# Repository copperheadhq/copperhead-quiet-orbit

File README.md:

# Quiet Orbit QO-R1

A USB-C powered desk ornament: four amber LEDs at the corners of a 40 mm square, each on its
own hardware-PWM channel of an ATtiny84A, fading independently on four phases. 57 × 57 mm,
two layers, no data, no PD, no radio, no battery, no controls.

> ## ⚠ This board has never been built
>
> No PCB has been fabricated from these files. Nothing has been powered on. The firmware has
> never been compiled, because no AVR toolchain was available where it was written, and it has
> never run on hardware. Every manufacturer part number in the BOM is marked **UNVERIFIED** by its own
> author, and at least one fitted part is known to be the wrong choice.
>
> The files pass ERC and DRC. That means the copper is consistent with the schematic and with
> a set of design rules. It is not evidence that the circuit works.
>
> **Do not order this board expecting a working lamp.** Order it to look at, to fork, or to
> fix.

Quick facts: [docs/QO-R1-summary.pdf](docs/QO-R1-summary.pdf). Everything: [docs/QO-R1-reference.pdf](docs/QO-R1-reference.pdf).

## Background

On 21 September 2026, Paras Chopra [posted](https://x.com/paraschopra/status/2101906787050115492)
that he had asked an AI model he calls Astra to design a piece of hardware for itself. It chose
four softly blinking lights powered by USB, and produced a PCB, a casing and an email to a
manufacturer.

The same day we gave that post to [copperhead](https://x.com/copperheadhq) as a brief and
[shared the result](https://x.com/animeshsingh38/status/2102001126682042727). This repository is
that build, with its source files. It is an independent design that started from the public post. No files, images or schematics
from the original project are used here.

## The circuit

Full sheet as [PDF](docs/schematic.pdf) or [SVG](docs/schematic.svg). Source of truth is
`hardware/*.kicad_sch`. The exports are generated from it.

## Layout of this repository

```text
hardware/           KiCad 10 project: schematic, 57 × 57 mm board, design rules,
                    project footprint and symbol libraries
  variant-milkyway/ alternative back with Milky Way artwork in copper, mask and silk
firmware/           AVR-GCC, ATtiny84A, two 8-bit timers driving four PWM channels
docs/               summary and reference PDFs, specification, subsystems, pinout, BOM,
                    design decisions, changelog, and the schematic as PDF and SVG
fab/                gerbers, drill, BOM and CPL (read the warning in that folder)
images/             renders of the board, not photographs
3d/                 STEP, GLB and STL models, including one for an enclosure designer
LICENSES/           full text of the three licences below
```

## Building it

**Hardware.** Open `hardware/*.kicad_pro` in KiCad 10.0.4 or newer. The project carries its own
symbol cache and footprint libraries, so it opens standalone.

**Firmware.** Needs `avr-gcc` and `avr-libc`:

```bash
make -C firmware        # produces quiet-orbit-qo-r1.hex for attiny84 at F_CPU=8000000UL
```

This has never been run. If it does not compile, please send a patch.

Flash through J2 with any AVR ISP programmer. The ATtiny84A arrives blank and runs on its
internal 8 MHz RC oscillator. There is no crystal and no regulator. If your part ships with the
clock divided by 8, change that fuse; nothing else needs changing.

## Licence

Three licences, by file type:

| What | Licence |
|---|---|
| Hardware: everything under `hardware/`, `fab/` and `3d/` | **CERN-OHL-S-2.0** (strongly reciprocal) |
| Software: `firmware/` | **GPL-3.0-only** |
| Documentation and images: `docs/`, `images/`, `README.md` | **CC-BY-4.0** |

Full texts are in [`LICENSES/`](LICENSES/). In short: you may make, modify, sell and fabricate
this, and if you distribute a modified board or modified firmware you must publish your sources
under the same terms. See [`LICENSE`](LICENSE) for the per-directory statement.

**Trademarks are not licensed.** The copperhead word mark and the snake lockup that appear on
the silkscreen are trademarks; the licences above cover the design, not the marks. If you
fabricate a modified board, remove them from the silkscreen.

**No warranty.** This is an unbuilt, unverified design. CERN-OHL-S-2.0 sections 8 and 9 apply:
no warranty, no liability. If you fabricate it, that decision is yours.

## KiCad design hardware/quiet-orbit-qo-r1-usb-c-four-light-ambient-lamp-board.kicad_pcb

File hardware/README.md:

# Hardware

KiCad 10 project for the Quiet Orbit QO-R1. Open `*.kicad_pro`.

This board has never been fabricated. The series diode D1 (1N4148W) is the wrong part for the
power path; a 1 A Schottky in the same SOD-123 footprint is the better fit.

| File | What |
|---|---|
| `*.kicad_sch` | schematic |
| | *(readable exports: `docs/schematic.pdf`, `docs/schematic.svg`)* |
| `*.kicad_pcb` | 57 × 57 mm, 2 layers |
| `*.kicad_dru` | custom design rules, described below |
| `*.kicad_pro` | project settings, including the rule set used for DRC |
| `schematic.intent.json` | the machine-readable intent the schematic was generated from |
| `sym-lib-table`, `sym-lib-cache/` | project symbols, so the project opens standalone |
| `libs/footprints/` | project footprint libraries, from the KiCad standard set |
| `variant-milkyway/` | alternative back with copper artwork |

## Design rules

Our own conservative set, not any named fab's: clearance 0.2 mm, track 0.25 mm signal and 0.5 mm on
the power rails, via 0.65 / 0.3 mm, copper to edge 0.4 mm, hole clearance 0.25 mm, silk text at
least 1.0 mm. No KiCad severity is changed from default and there are no DRC exclusions.

One scoped rule is in the `.kicad_dru`: hole clearance 0.19 mm between J1 and itself. The
USB-C receptacle's stock land pattern puts its GND pads 0.194 mm from its own locating-peg
holes, which is four errors on any board using that footprint at the board-wide 0.25 mm. The
board-wide rule is untouched. A fab with a hard 0.2 mm NPTH-to-copper limit will query it.

Every two-pad part also carries a thin no-track rule area across its pad gap. This was added
after the autorouter put a track between the pads of an 0603. That passed DRC but is poor
practice.

## Geometry

57 × 57 mm. LED optical centres on a board-centred 40 mm square (NW, NE, SE, SW). Four M3
NPTH holes, each centre 4 mm from both adjacent edges. USB-C centred on one edge and flush
with it. All populated parts on the top side.

57 mm is close to the geometric floor for this brief: at 56.5 mm the LED and M3 courtyards are
0.13 mm apart, and at 56.0 mm they overlap. Going smaller means moving the mounting holes
inside the LED square or abandoning the 40 mm pitch.

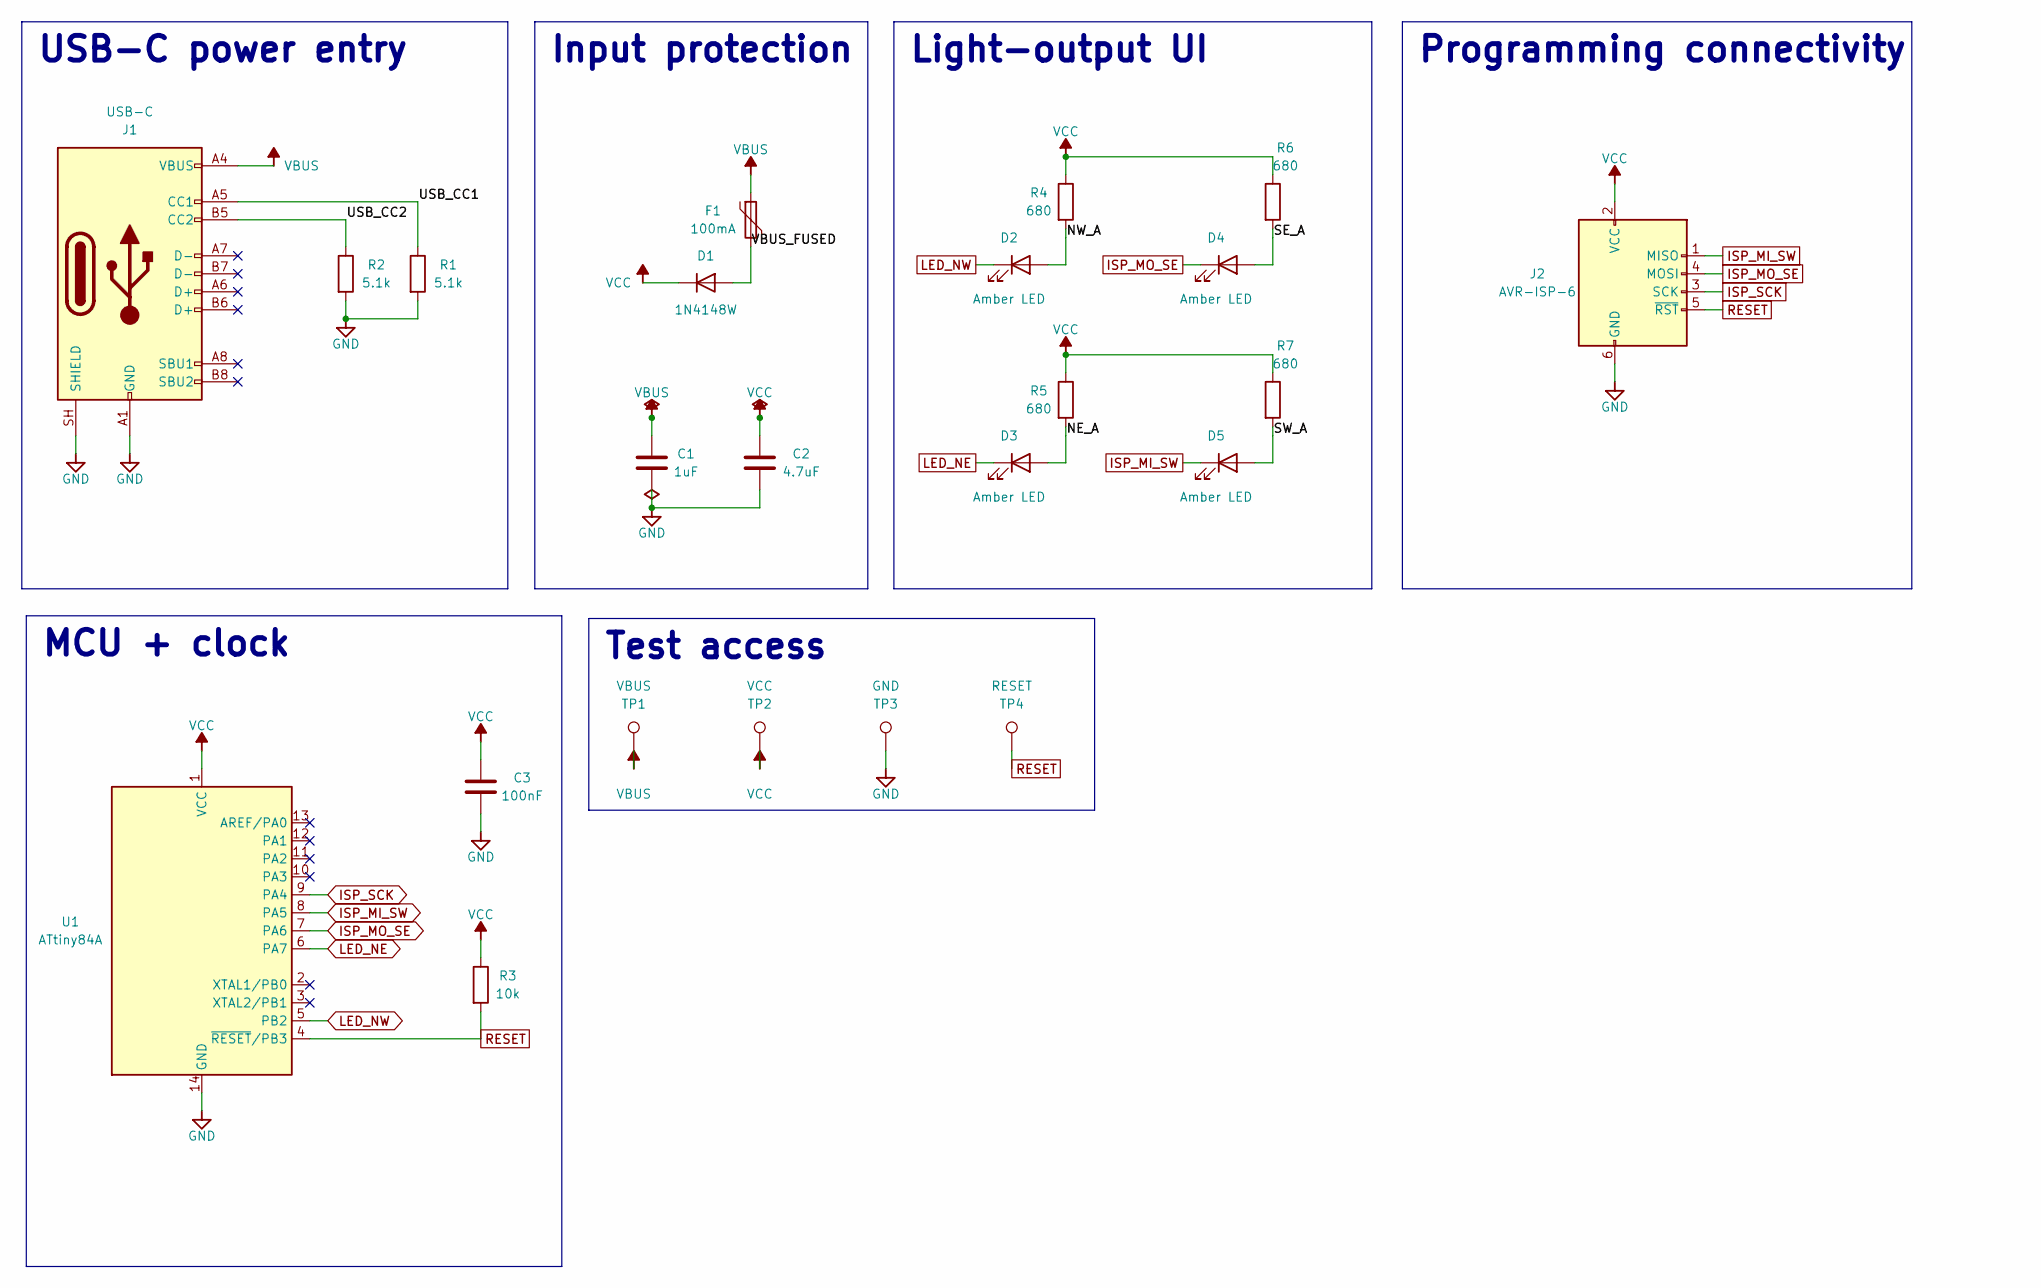
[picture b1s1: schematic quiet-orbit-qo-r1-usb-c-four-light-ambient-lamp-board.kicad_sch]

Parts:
C1: 1uF; C_0603_1608Metric
C2: 4.7uF; C_0805_2012Metric
C3: 100nF; C_0603_1608Metric
D1: 1N4148W; D_SOD-123
D2, D3, D4, D5: Amber LED; LED_1206_3216Metric
F1: 100mA; Fuse_0603_1608Metric
J1: USB-C; USB_C_Receptacle_GCT_USB4105-xx-A_16P_TopMnt_Horizontal
J2: AVR-ISP-6; IDC-Header_2x03_P2.54mm_Vertical
R1, R2: 5.1k; R_0603_1608Metric
R3: 10k; R_0603_1608Metric
R4, R5, R6, R7: 680; R_0603_1608Metric
TP1: VBUS; TestPoint_Pad_D1.5mm
TP2: VCC; TestPoint_Pad_D1.5mm
TP3: GND; TestPoint_Pad_D1.5mm
TP4: RESET; TestPoint_Pad_D1.5mm
U1: ATtiny84A; SOIC-14_3.9x8.7mm_P1.27mm

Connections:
/NE_A: D3.2 (A), R5.2
/NW_A: D2.2 (A), R4.2
/SE_A: D4.2 (A), R6.2
/SW_A: D5.2 (A), R7.2
/USB_CC1: J1.A5 (CC1), R1.1
/USB_CC2: J1.B5 (CC2), R2.1
/VBUS_FUSED: D1.2 (A), F1.2
GND: C1.2, C2.2, C3.2, J1.A1 (GND), J1.A12 (GND), J1.B1 (GND), J1.B12 (GND), J1.SH (SHIELD), J2.6 (GND), R1.2, R2.2, TP3.1, U1.14 (GND)
ISP_MI_SW: D5.1 (K), J2.1 (MISO), U1.8 (PA5)
ISP_MO_SE: D4.1 (K), J2.4 (MOSI), U1.7 (PA6)
ISP_SCK: J2.3 (SCK), U1.9 (PA4)
LED_NE: D3.1 (K), U1.6 (PA7)
LED_NW: D2.1 (K), U1.5 (PB2)
RESET: J2.5 (~RST), R3.2, TP4.1, U1.4 (~RESET/PB3)
VBUS: C1.1, F1.1, J1.A4 (VBUS), J1.A9 (VBUS), J1.B4 (VBUS), J1.B9 (VBUS), TP1.1
VCC: C2.1, C3.1, D1.1 (K), J2.2 (VCC), R3.1, R4.1, R5.1, R6.1, R7.1, TP2.1, U1.1 (VCC)

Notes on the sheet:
Programming connectivity
Input protection
Light-output UI
USB-C power entry
MCU + clock
Test access

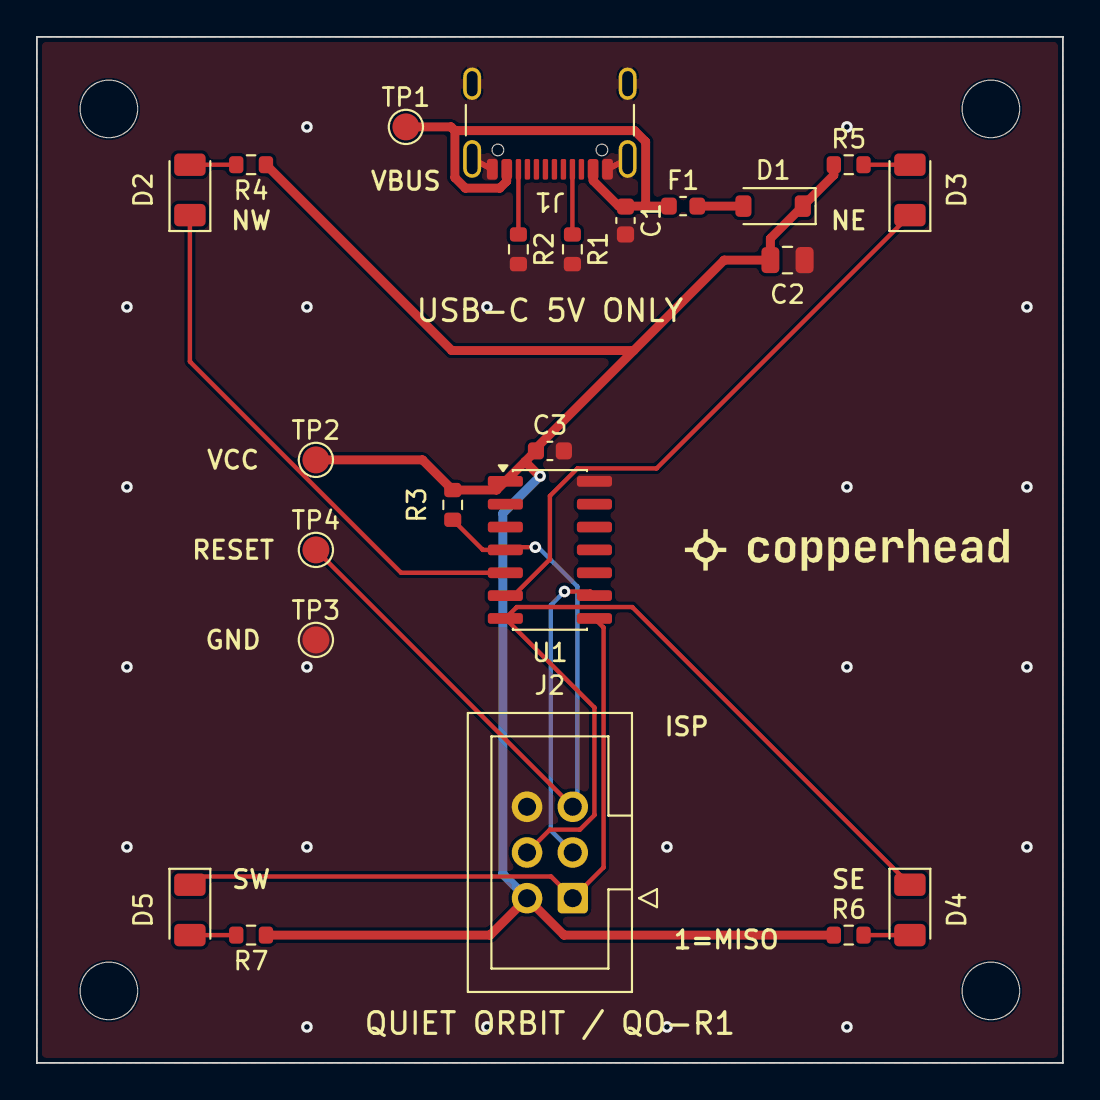
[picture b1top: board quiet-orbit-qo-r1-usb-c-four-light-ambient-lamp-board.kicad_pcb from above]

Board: 2 copper layers, 57.0 x 57.0 mm, 27 parts (0 on the bottom side), 16 nets.

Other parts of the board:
H1, H2, H3, H4: M3; MountingHole_3.2mm_M3

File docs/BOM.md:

# Quiet Orbit QO-R1 Bill of Materials

Every purchasable MPN below is **UNVERIFIED** pending review of the current manufacturer datasheet, distributor stock, lifecycle status, and footprint drawing before release. Each rationale states the properties to verify. Value entries contain schematic component values only.

| Refdes | Value | Footprint | MPN | Rationale |
|---|---|---|---|---|
| J1 | USB-C | Connector_USB:USB_C_Receptacle_GCT_USB4105-xx-A_16P_TopMnt_Horizontal | USB4105-GF-A (UNVERIFIED) | Power-only 16-pin receptacle; verify VBUS, GND, CC, shell, edge-flush geometry, rating, and footprint. Installed `Connector:USB_C_Receptacle_USB2.0_16P` is one unit with confirmed A/B package pins and SH. |
| F1 | 100mA | Fuse:Fuse_0603_1608Metric | MF-FSMF010X-2 (UNVERIFIED) | Verify 100 mA hold, at least 200 mA trip at 25 °C, voltage, resistance, tolerance, derating, and footprint. No quiescent current beyond series loss. Installed `Device:Polyfuse` has pins 1 and 2. |
| D1 | 1N4148W | Diode_SMD:D_SOD-123 | 1N4148W-7-F (UNVERIFIED) | Silicon reverse blocker; verify no more than 10 µA reverse leakage at room temperature and 5 V, no more than 0.8 V forward drop near 20 mA, rating, polarity, and package. Installed diode mapping uses pin 1 K and pin 2 A. |
| C1 | 1uF | Capacitor_SMD:C_0603_1608Metric | CC0603KRX7R9BB105 (UNVERIFIED) | Verify capacitance, X7R dielectric, rating, tolerance, DC-bias loss, leakage, and footprint. The 1 µF receptacle-side value is below the 10 µF limit. |
| C2 | 4.7uF | Capacitor_SMD:C_0805_2012Metric | GRM21BR71A475KA73L (UNVERIFIED) | Verify X7R, at least 10 V rating, tolerance, leakage, footprint, and more than 1 µF retained capacitance at operating bias. |
| C3 | 100nF | Capacitor_SMD:C_0603_1608Metric | CC0603KRX7R9BB104 (UNVERIFIED) | MCU bypass; verify X7R, rating, tolerance, leakage, and footprint; place directly at U1 VCC/GND. |
| R1 | 5.1k | Resistor_SMD:R_0603_1608Metric | RC0603FR-075K1L (UNVERIFIED) | Independent CC1 Rd; verify value, 1% tolerance, rating, and footprint. Worst-case draw is about 1.03 mA at 5.25 V and -1% tolerance. |
| R2 | 5.1k | Resistor_SMD:R_0603_1608Metric | RC0603FR-075K1L (UNVERIFIED) | Independent CC2 Rd; verify value, 1% tolerance, rating, and footprint. Worst-case draw is about 1.03 mA. |
| R3 | 10k | Resistor_SMD:R_0603_1608Metric | RC0603FR-0710KL (UNVERIFIED) | RESET pull-up; verify value, 1% tolerance, rating, and footprint. Normal draw is negligible; RESET-low draw is at most about 0.525 mA. |
| U1 | ATtiny84A | Package_SO:SOIC-14_3.9x8.7mm_P1.27mm | ATTINY84A-SSUR (UNVERIFIED) | Verify 5 V operation, 8 MHz internal RC, supply-current maximum, PWM/ISP functions, lifecycle, and SOIC-14 drawing. Installed one-unit `MCU_Microchip_ATtiny:ATtiny84A-P` has the compatible 14-pin numbering: VCC 1, RESET/PB3 4, PA7..PA0 6..13, GND 14. Budget reserves 10 mA pending datasheet confirmation. |
| D2 | Amber LED | LED_SMD:LED_1206_3216Metric | 150120AS75000 (UNVERIFIED) | NW LED; verify 590–605 nm, forward-voltage bounds at 2–5 mA, optical consistency, polarity, and 1206 package. Installed `Device:LED` uses pin 1 K and pin 2 A. |
| D3 | Amber LED | LED_SMD:LED_1206_3216Metric | 150120AS75000 (UNVERIFIED) | NE LED; same datasheet checks as D2. |
| D4 | Amber LED | LED_SMD:LED_1206_3216Metric | 150120AS75000 (UNVERIFIED) | SE LED; same datasheet checks as D2. |
| D5 | Amber LED | LED_SMD:LED_1206_3216Metric | 150120AS75000 (UNVERIFIED) | SW LED; same datasheet checks as D2. |
| R4 | 680 | Resistor_SMD:R_0603_1608Metric | RC0603FR-07680RL (UNVERIFIED) | NW LED resistor; verify value, 1% tolerance, rating, and footprint. With 4.75–5.25 V VBUS, 0.5–0.8 V D1 drop, 1.8–2.4 V LED drop, and resistor tolerance, current is about 2.26–4.38 mA; repeat using verified limits. |
| R5 | 680 | Resistor_SMD:R_0603_1608Metric | RC0603FR-07680RL (UNVERIFIED) | NE LED resistor; same provisional 2.26–4.38 mA calculation and checks as R4. |
| R6 | 680 | Resistor_SMD:R_0603_1608Metric | RC0603FR-07680RL (UNVERIFIED) | SE LED resistor; same provisional 2.26–4.38 mA calculation and checks as R4. |
| R7 | 680 | Resistor_SMD:R_0603_1608Metric | RC0603FR-07680RL (UNVERIFIED) | SW LED resistor; same provisional 2.26–4.38 mA calculation and checks as R4. |
| J2 | AVR-ISP-6 | Connector_IDC:IDC-Header_2x03_P2.54mm_Vertical | 61200621621 (UNVERIFIED) | Verify 2 × 3 positions, 2.54 mm pitch, numbering, key, height, footprint, and pin-1 marking. Installed `Connector_Generic:Conn_02x03_Odd_Even` is one unit with pins 1–6. VCC is sense-only. |
| TP1 | VBUS | TestPoint:TestPoint_Pad_D1.5mm | DNP | Bare PCB pad; no purchased MPN. Installed `Connector:TestPoint` has pin 1. The 1.5 mm pad exceeds the 1.0 mm minimum; preserve 0.5 mm clearance. |
| TP2 | VCC | TestPoint:TestPoint_Pad_D1.5mm | DNP | Bare protected-VCC PCB pad; same symbol and mechanical checks as TP1. |
| TP3 | GND | TestPoint:TestPoint_Pad_D1.5mm | DNP | Bare GND PCB pad; same symbol and mechanical checks as TP1. |
| TP4 | RESET | TestPoint:TestPoint_Pad_D1.5mm | DNP | Bare RESET PCB pad; same symbol and mechanical checks as TP1. |

## Electrical budget closure

- CC termination worst case is approximately 2.06 mA total.
- U1 reserves 10 mA pending datasheet confirmation. Allowing another 1 mA for all passive leakage and margin gives a provisional 13.06 mA non-LED total, below 20 mA.
- Four LED channels at the provisional 4.38 mA maximum total 17.52 mA, below 20 mA.
- The provisional expected maximum is 30.58 mA, below the 40 mA ceiling and strict 100 mA USB limit. Final release requires replacing every UNVERIFIED check with current datasheet and distributor evidence.
- D1 is the intentional reverse-current element; its exact maximum leakage at 5 V and room temperature must be confirmed as no more than 10 µA.

## Symbol and capture notes

Installed-library searches and pin inspections were completed for U1, J1, J2, D1, D2–D5, F1, and TP1–TP4. All selected symbols are single-unit. Resistors and capacitors use standard `Device:R` and `Device:C`. J1 D+, D−, SBU1, and SBU2 are intentionally unconnected because the product is power-only.

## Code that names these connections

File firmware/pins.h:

#ifndef QO_R1_PINS_H
#define QO_R1_PINS_H

#include <avr/io.h>

/* Generated from docs/PINOUT.md; do not assign board pins elsewhere. */
#define QO_MCU_PART                 ATtiny84A
#define QO_CPU_HZ                   8000000UL

/* U1.5: PB2 / OC0A, net LED_NW. */
#define LED_NW_DDR                  DDRB
#define LED_NW_PORT                 PORTB
#define LED_NW_BIT                  PB2
#define LED_NW_OCR                  OCR0A

/* U1.6: PA7 / OC0B, net LED_NE. */
#define LED_NE_DDR                  DDRA
#define LED_NE_PORT                 PORTA
#define LED_NE_BIT                  PA7
#define LED_NE_OCR                  OCR0B

/* U1.7: PA6 / MOSI / OC1A, net ISP_MO_SE. */
#define LED_SE_DDR                  DDRA
#define LED_SE_PORT                 PORTA
#define LED_SE_BIT                  PA6
#define LED_SE_OCR                  OCR1A
#define ISP_MOSI_DDR                DDRA
#define ISP_MOSI_PORT               PORTA
#define ISP_MOSI_BIT                PA6

/* U1.8: PA5 / MISO / OC1B, net ISP_MI_SW. */
#define LED_SW_DDR                  DDRA
#define LED_SW_PORT                 PORTA
#define LED_SW_BIT                  PA5
#define LED_SW_OCR                  OCR1B
#define ISP_MISO_DDR                DDRA
#define ISP_MISO_PORT               PORTA
#define ISP_MISO_BIT                PA5

/* U1.9: PA4 / SCK, net ISP_SCK. */
#define ISP_SCK_DDR                 DDRA
#define ISP_SCK_PORT                PORTA
#define ISP_SCK_BIT                 PA4

/* U1.4: PB3 / RESET, net RESET; fuse-controlled reset input. */
#define RESET_DDR                   DDRB
#define RESET_PORT                  PORTB
#define RESET_BIT                   PB3

/* U1.2, U1.3, U1.10-U1.13 are NC by design. */

#endif
